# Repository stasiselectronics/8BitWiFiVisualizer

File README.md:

# 8 Bit WiFi Visualizer
Open Source Hardware project for a minimalist WiFi enabled 8 Bit visualizer. This design uses the popular ESP8266 wifi module to drive 8 LEDs with a shift register.
<h2><a href="https://stasiselectronics.github.io/8BitWiFiVisualizer/docs/">Check out the Docs!</a></h2>
<h2><a href="https://www.tindie.com/products/stasis/8-bit-wifi-visualizer/">Order on Tindie!</a></h2>

## Network Traffic Visualizer
Want to visualize how busy your WiFi channel is? The included Arduino sketch measures how many packets are flying around on the selected channel and displays the intensity on the LEDs.

With the help of some automated functions, the board selects the WiFi channel with the strongest network present at startup. It then automatically adjusts the display range to keep up with changing network conditions.

[Learn more about how this firmware works!](https://stasiselectronics.github.io/8BitWiFiVisualizer/docs/enclosure/automatic-firmware/)

This repository contains all the source files needed to reproduce this project. The PCB is designed with KiCAD and the firmware uses Arduino for the ESP8266.

This is still a work in progress, so be sure to check back for future updates!

## Companion Site
I've put together a Github pages site to host all the documentation that goes with this design. Learn more about how everything works and keep up to date with blog posts. 

<h4>This is still a work in progress, more to come!</h4>

[Check out the companion site for more documentation!](https://stasiselectronics.github.io/8BitWiFiVisualizer/)

## Quick Links
- [Board Schematics](https://github.com/stasiselectronics/8BitWiFiVisualizer/blob/master/Hardware%20Files/PDFs/8Bit_WiFi_Visualizer_Schematic.pdf)
- [Arduino Sketch](https://github.com/stasiselectronics/8BitWiFiVisualizer/blob/master/Firmware%20Files/PacketVisualizer_auto/PacketVisualizer_auto.ino)

## Current Status

This project is nearing completion, here are some of the latest updates
- Redesigned PCB for larger components to make hand soldering easier
- Assembled and tested latest PCB design
- Major firmware updates
    - Auto selecting AP channel on startup
    - Auto ranging intensity scale with linear decay
    - Change AP channel with user button

## Future Goals

Here's what needs to get done for this project:
- Complete Documentation

Most of the project is now complete, so now all that is left is to finish up the documentation

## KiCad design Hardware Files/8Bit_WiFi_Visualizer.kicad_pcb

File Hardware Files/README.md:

# Hardware Files

Here you can find all the files for the PCB design. The board is designed in KiCAD

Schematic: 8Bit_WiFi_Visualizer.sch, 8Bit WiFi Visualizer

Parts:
C1, C2, C4, C5: 1uF; C_1206_3216Metric_Pad1.42x1.75mm_HandSolder; Manufacturer PN CL31B105KCHNNNE; LCSC Order Number C13832
C3: 10uF; C_1206_3216Metric_Pad1.42x1.75mm_HandSolder; Manufacturer PN CL31B106KAHNNNE; LCSC Order Number C14860
D1, D2, D3, D4, D5, D6, D7, D8: LED; LED_1206_3216Metric_Pad1.42x1.75mm_HandSolder; Manufacturer PN LTST-C150TBKT; LCSC Order Number C125088
J1: USB_B_Micro; U-F-M5DD-Y-L; Manufacturer PN U-F-M5DD-Y-L; LCSC Order Number C91146
J2: Conn_01x04; PinHeader_1x04_P2.54mm_Vertical
J3, J4: Conn_01x01; MountingHole_3.2mm_M3_DIN965_Pad
R1, R2, R3, R4, R5: 10k; R_1206_3216Metric_Pad1.42x1.75mm_HandSolder; Manufacturer PN RC1206JR-0710KL; LCSC Order Number C136460
SW1: SW_Push_Dual; PTS645SK50SMTR92LFS; Manufacturer PN 1TS005F-2500-5001; LCSC Order Number C255812
SW2, SW3: SW_SPST; PTS636_SM25F_SMTR_LFS; Manufacturer PN 1TS002B-2700-5000-CT; LCSC Order Number C318844
U1: 3.3V 1A; SOT-223-3_TabPin2; Manufacturer PN AZ1117CH-3.3TRG1; LCSC Order Number C92102
U2: 74HC595; SOIC-16_3.9x9.9mm_P1.27mm; Manufacturer PN 74HC595D,118; LCSC Order Number C5947
U3: ESP-WROOM-02D; Manufacturer PN ESP-WROOM-02D; LCSC Order Number C473007

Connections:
+3V3: C2.1, C3.1, C4.1, R1.1, R2.1, R5.1, U1.2 (VO), U2.16 (VCC), U3.1
+5V: C1.1, J1.1 (VBUS), J2.1, U1.3 (VI)
/BOOT: R1.2, SW3.1 (A), U3.8
/CLEAR: U2.10 (~SRCLR), U3.4
/CLOCK: U2.11 (SRCLK), U3.10
/DATA: U2.14 (SER), U3.17
/ESP_EN: C5.1, R2.2, SW2.1 (A), U3.2
/ESP_RX: J2.3, U3.11
/ESP_TX: J2.2, U3.12
/LATCH: U2.12 (RCLK), U3.14
/LED_1: D1.2 (A), U2.15 (QA)
/LED_2: D2.2 (A), U2.1 (QB)
/LED_3: D3.2 (A), U2.2 (QC)
/LED_4: D4.2 (A), U2.3 (QD)
/LED_5: D5.2 (A), U2.4 (QE)
/LED_6: D6.2 (A), U2.5 (QF)
/LED_7: D7.2 (A), U2.6 (QG)
/LED_8: D8.2 (A), U2.7 (QH)
/OUTPUT_ENABLE: R3.2, U2.13 (~OE), U3.5
/RST: U3.15
/SW_1: R5.2, SW1.1, SW1.3, U3.3
GND: C1.2, C2.2, C3.2, C4.2, C5.2, D1.1 (K), D2.1 (K), D3.1 (K), D4.1 (K), D5.1 (K), D6.1 (K), D7.1 (K), D8.1 (K), J1.5 (GND), J1.6 (Shield), J2.4, J3.1, J4.1, R3.1, R4.2, SW1.2, SW1.4, SW2.2 (B), SW3.2 (B), U1.1 (GND), U2.8 (GND), U3.9, U3.13, U3.18, U3.19
unnamed: R4.1, U3.6

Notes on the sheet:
External pull down on GPIO15 for boot options
It is recommended that users do not solder Pad 19 to the base board. If users do want to solder it, they need to ensure that the correct quantity of soldering paste is applied.
Programming
User Switch
3.3V Power Supply
LED Driver
ESP8266 MCU
LEDs
Programming Header

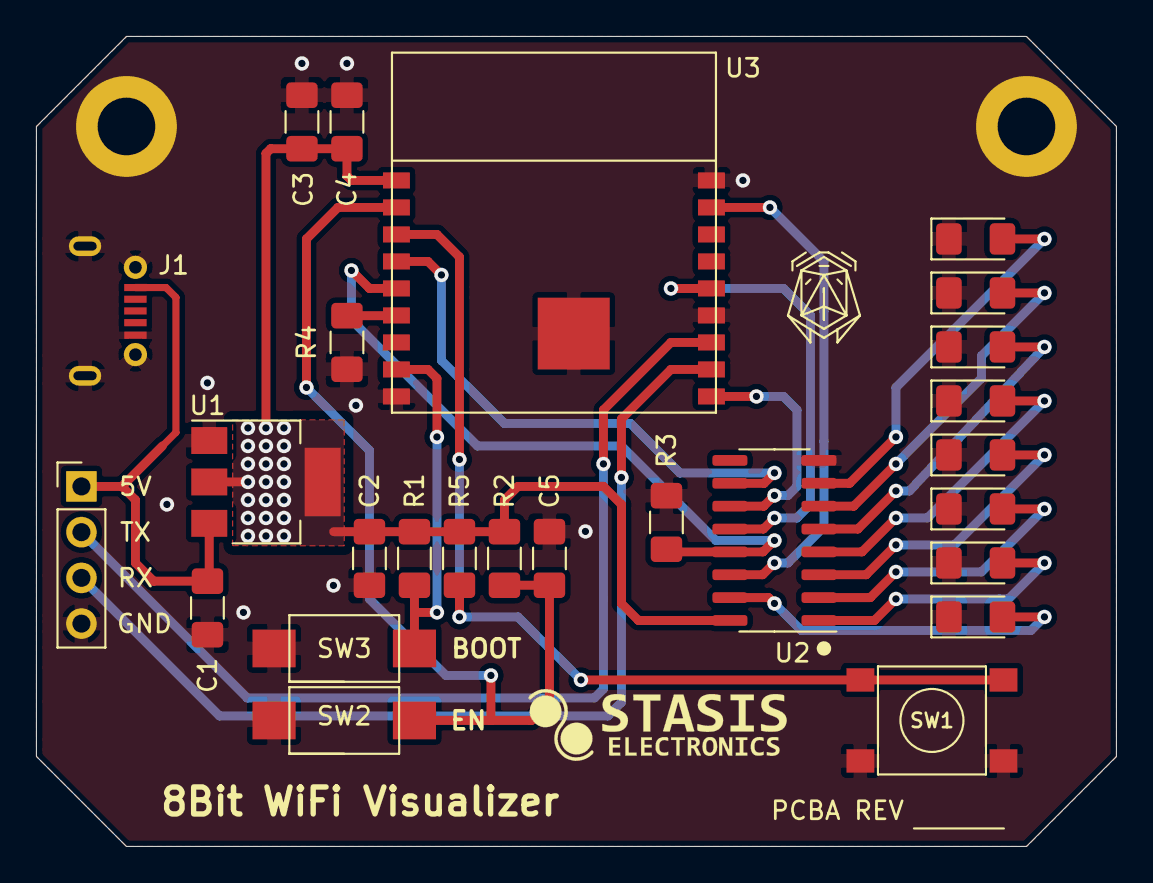
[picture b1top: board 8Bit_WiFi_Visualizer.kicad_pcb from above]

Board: 2 copper layers, 60.0 x 45.0 mm, 28 parts (0 on the bottom side), 22 nets.

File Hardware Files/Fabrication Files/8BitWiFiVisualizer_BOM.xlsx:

Component | References | Value | Description | LCSC Order Number | Manufacturer | Manufacturer PN | Quantity Per PCB | QTY per 100
1 | C1 C2 C4 C5 | 1uF | Unpolarized capacitor, small symbol | C13832 | Samsung Electro-Mechanics | CL31B105KCHNNNE | 4 | 400
2 | C3 | 10uF | Unpolarized capacitor, small symbol | C14860 | Samsung Electro-Mechanics | CL31B106KAHNNNE | 1 | 100
3 | D1 D2 D3 D4 D5 D6 D7 D8 | LED | Light emitting diode | C125088 | Lite-On | LTST-C150TBKT | 8 | 800
4 | J2 | Conn_01x04 | Generic connector, single row, 01x04 | C358686 | MINTRON | MTP125-1104S1 | 1 | 100
5 | J1 | USB_B_Micro | USB Micro Type B connector | C91146 | Korean Hroparts Elec | U-F-M5DD-Y-L | 1 | 100
6 | R1 R2 R3 R4 R5 | 10k | Resistor | C136460 | YAGEO | RC1206JR-0710KL | 5 | 500
7 | SW1 | SW_Push_Dual | Push button switch, generic, symbol, four pins | C255812 | Hongyuan Precision | 1TS005F-2500-5001 | 1 | 100
8 | SW2 SW3 | SW_SPST | Single Pole Single Throw (SPST) switch | C318844 | Hongyuan Precision | 1TS002B-2700-5000-CT | 2 | 200
9 | U1 | 3.3V 1A | 1A Low Dropout regulator, positive, 3.3V fixed output, SOT-223 | C92102 | Diodes Incorporated | AZ1117CH-3.3TRG1 | 1 | 100
10 | U2 | 74HC595 | 8-bit serial in/out Shift Register 3-State Outputs | C5947 | Nexperia | 74HC595D,118 | 1 | 100
11 | U3 | ESP-WROOM-02D |  | C473007 | Espressif Systems | ESP-WROOM-02D | 1 | 100

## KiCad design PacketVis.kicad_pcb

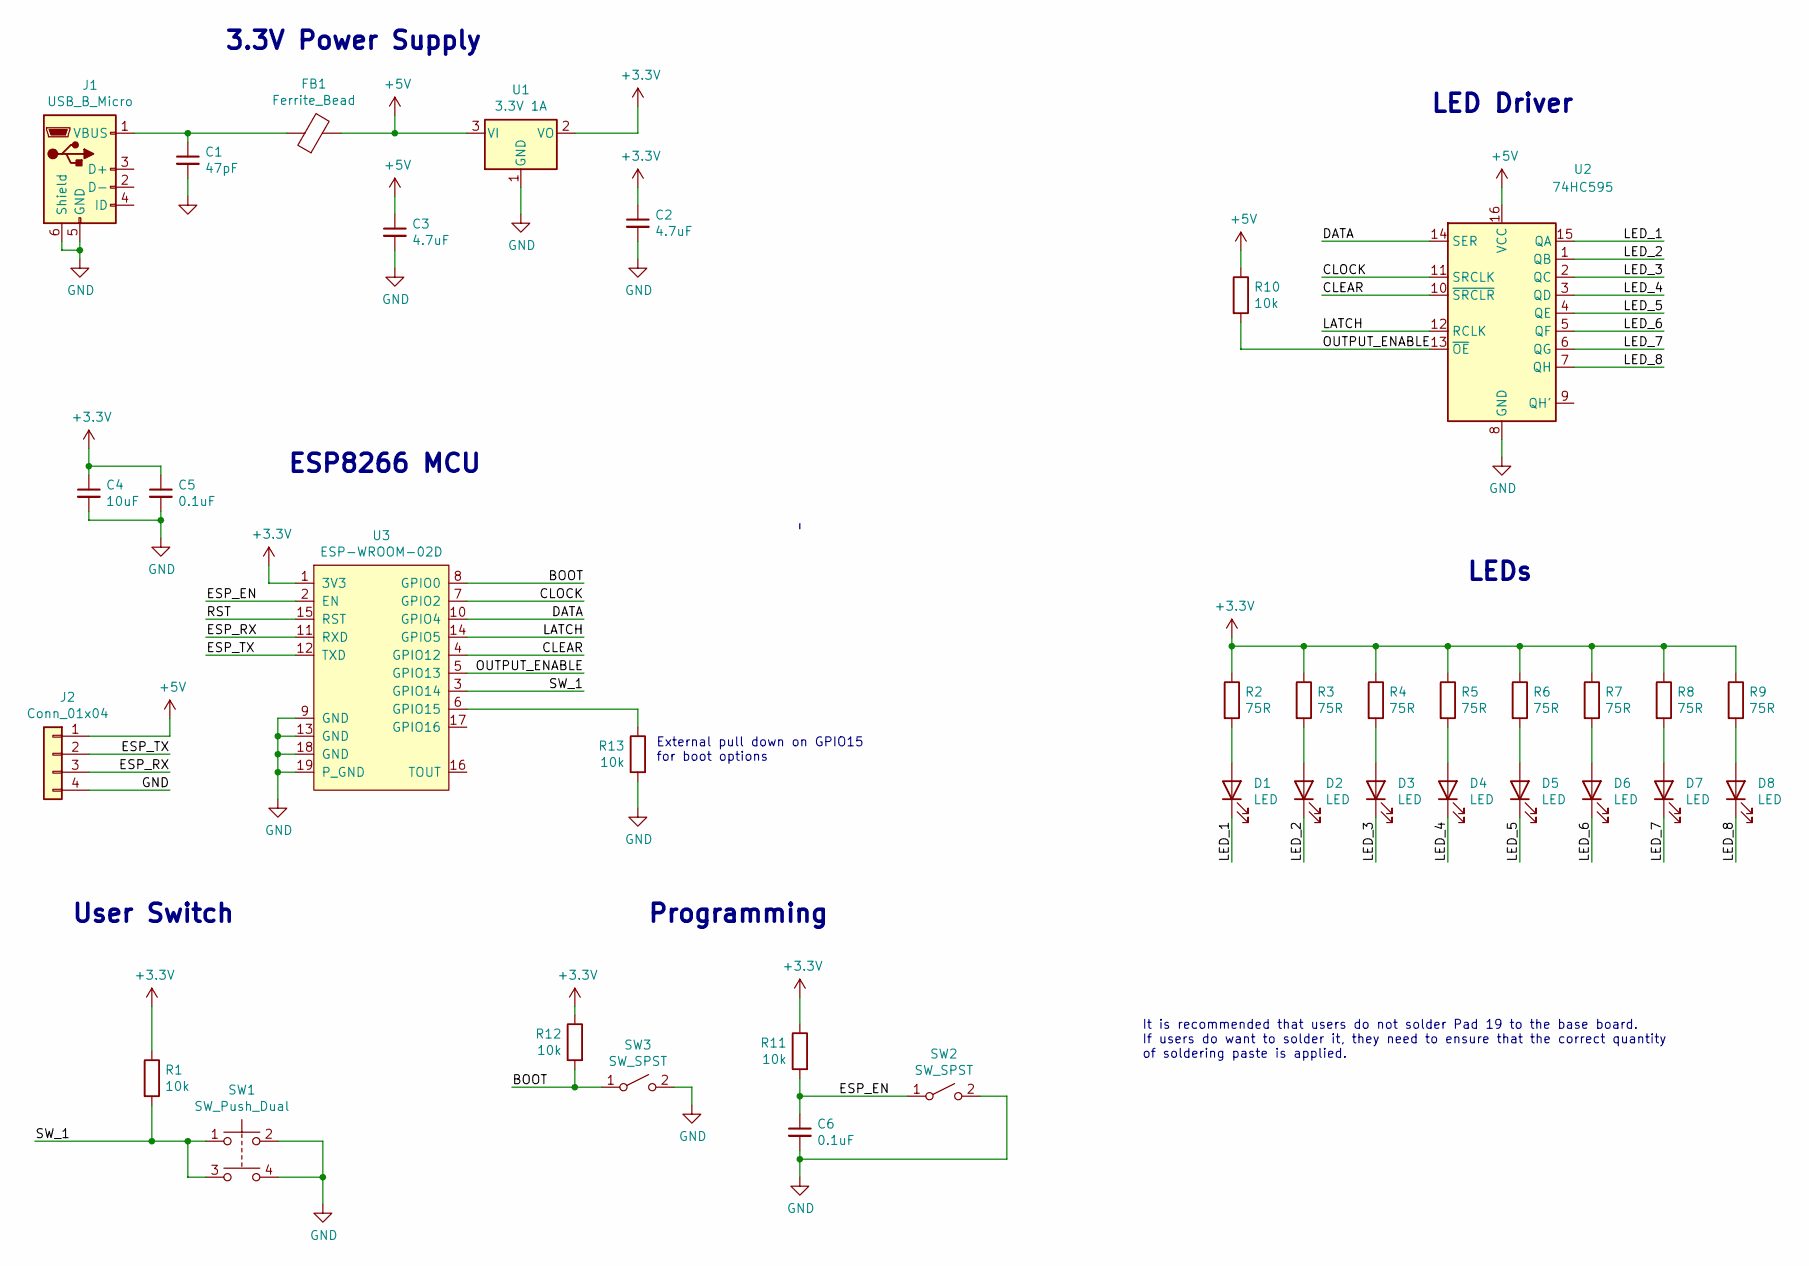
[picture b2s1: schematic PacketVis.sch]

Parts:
C1: 47pF; C_0805_2012Metric; Manufacturer PN CC0805JRNPO9BN470
C2, C3: 4.7uF; C_0805_2012Metric; Manufacturer PN CC0805ZRY5V6BB475
C4: 10uF; C_0805_2012Metric; Manufacturer PN CC0805ZKY5V5BB106
C5, C6: 0.1uF; C_0805_2012Metric; Manufacturer PN CC0805ZRY5V9BB104
D1, D2, D3, D4, D5, D6, D7, D8: LED; LED_0805_2012Metric_Castellated; Manufacturer PN LH R974-LP-1
FB1: Ferrite_Bead; L_0805_2012Metric; Manufacturer PN HI0805R800R-10
J1: USB_B_Micro; USB_Micro-B_Molex-105017-0001; Manufacturer PN 1050170001
J2: Conn_01x04; PinHeader_1x04_P2.54mm_Vertical
R1, R10, R11, R12, R13: 10k; R_0805_2012Metric; Manufacturer PN RC0805JR-0710KL
R2, R3, R4, R5, R6, R7, R8, R9: 75R; R_0805_2012Metric; Manufacturer PN RC0805FR-0775RL
SW1: SW_Push_Dual; PTS645SK50SMTR92 LFS; Manufacturer PN PTS645SK50SMTR92 LFS
SW2, SW3: SW_SPST; PTS636_SM25F_SMTR_LFS; Manufacturer PN PTS636 SM25F SMTR LFS
U1: 3.3V 1A; SOT-223-3_TabPin2; Manufacturer PN AP2114H-3.3TRG1
U2: 74HC595; SOIC-16; Manufacturer PN SN74HC595DR
U3: ESP-WROOM-02D; Manufacturer PN ESP-WROOM-02D

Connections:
+3V3: C2.1, C4.1, C5.1, R1.1, R2.1, R3.1, R4.1, R5.1, R6.1, R7.1, R8.1, R9.1, R11.1, R12.1, U1.2 (VO), U3.1 (3V3)
+5V: C3.1, FB1.2, J2.1, R10.1, U1.3 (VI), U2.16 (VCC)
/BOOT: R12.2, SW3.1 (A), U3.8 (GPIO0)
/CLEAR: U2.10 (~SRCLR), U3.4 (GPIO12)
/CLOCK: U2.11 (SRCLK), U3.7 (GPIO2)
/DATA: U2.14 (SER), U3.10 (GPIO4)
/ESP_EN: C6.1, R11.2, SW2.1 (A), U3.2 (EN)
/ESP_RX: J2.3, U3.11 (RXD)
/ESP_TX: J2.2, U3.12 (TXD)
/LATCH: U2.12 (RCLK), U3.14 (GPIO5)
/LED_1: D1.1 (K), U2.15 (QA)
/LED_2: D2.1 (K), U2.1 (QB)
/LED_3: D3.1 (K), U2.2 (QC)
/LED_4: D4.1 (K), U2.3 (QD)
/LED_5: D5.1 (K), U2.4 (QE)
/LED_6: D6.1 (K), U2.5 (QF)
/LED_7: D7.1 (K), U2.6 (QG)
/LED_8: D8.1 (K), U2.7 (QH)
/OUTPUT_ENABLE: R10.2, U2.13 (~OE), U3.5 (GPIO13)
/RST: U3.15 (RST)
/SW_1: R1.2, SW1.1, SW1.3, U3.3 (GPIO14)
GND: C1.2, C2.2, C3.2, C4.2, C5.2, C6.2, J1.5 (GND), J1.6 (Shield), J2.4, R13.2, SW1.2, SW1.4, SW2.2 (B), SW3.2 (B), U1.1 (GND), U2.8 (GND), U3.9 (GND), U3.13 (GND), U3.18 (GND), U3.19 (P_GND)
unnamed: C1.1, FB1.1, J1.1 (VBUS)
unnamed: D1.2 (A), R2.2
unnamed: D2.2 (A), R3.2
unnamed: D3.2 (A), R4.2
unnamed: D4.2 (A), R5.2
unnamed: D5.2 (A), R6.2
unnamed: D6.2 (A), R7.2
unnamed: D7.2 (A), R8.2
unnamed: D8.2 (A), R9.2
unnamed: R13.1, U3.6 (GPIO15)

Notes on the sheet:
External pull down on GPIO15 for boot options
It is recommended that users do not solder Pad 19 to the base board. If users do want to solder it, they need to ensure that the correct quantity of soldering paste is applied.
Programming
User Switch
3.3V Power Supply
LED Driver
ESP8266 MCU
LEDs

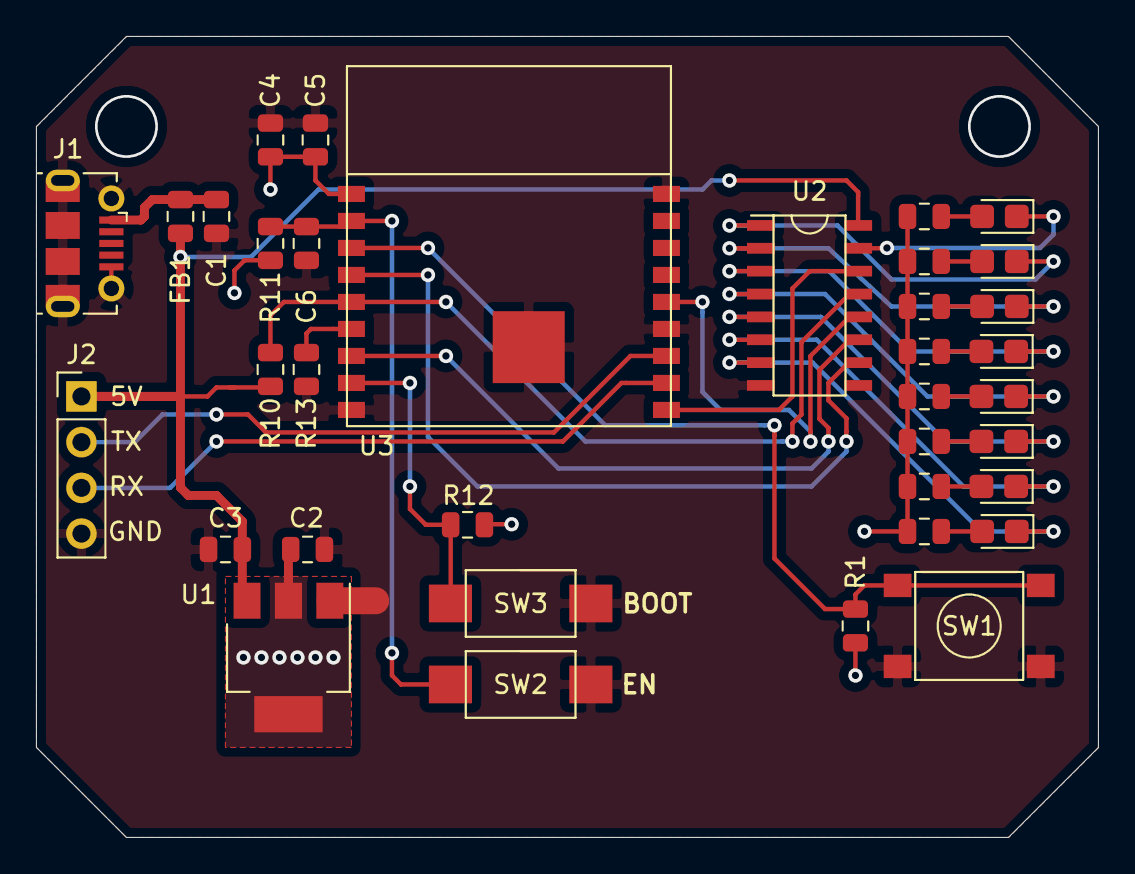
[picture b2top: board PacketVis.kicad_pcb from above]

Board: 2 copper layers, 59.0 x 44.5 mm, 36 parts (0 on the bottom side), 31 nets.

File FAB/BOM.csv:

C1,47pF,Capacitor_SMD:C_0805_2012Metric,~,CC0805JRNPO9BN470,1
">  C2, C3",4.7uF,Capacitor_SMD:C_0805_2012Metric,~,CC0805ZRY5V6BB475,2
    C4,10uF,Capacitor_SMD:C_0805_2012Metric,~,CC0805ZKY5V5BB106,1
">  C5, C6",0.1uF,Capacitor_SMD:C_0805_2012Metric,~,CC0805ZRY5V9BB104,2
>  D1-D8,LED,LED_SMD:LED_0805_2012Metric_Castellated,~,LH R974-LP-1,8
    FB1,Ferrite_Bead,Inductor_SMD:L_0805_2012Metric,~,HI0805R800R-10,1
    J1,USB_B_Micro,Connector_USB:USB_Micro-B_Molex-105017-0001,~,1050170001,1
    J2,Conn_01x03,Connector_PinHeader_2.54mm:PinHeader_1x03_P2.54mm_Vertical,~,,1
">  R1, R10-R13",10k,Resistor_SMD:R_0805_2012Metric,~,RC0805JR-0710KL,5
>  R2-R9,75R,Resistor_SMD:R_0805_2012Metric,~,RC0805FR-0775RL,8
    SW1,SW_Push_Dual,beginner_project_1_footprint_library:PTS645SK50SMTR92 LFS,~,PTS645SK50SMTR92 LFS,1
">  SW2, SW3",SW_SPST,beginner_project_1_footprint_library:PTS636_SM25F_SMTR_LFS,file:///C:/Users/A552123/Documents/KiCad%20Projects/beginner_project_1/beginner_project_1_footprint_library.pretty/datasheet.pdf,PTS636 SM25F SMTR LFS,2
    U1,3.3V 1A,Package_TO_SOT_SMD:SOT-223-3_TabPin2,https://www.diodes.com/assets/Datasheets/AP2114.pdf,AP2114H-3.3TRG1,1
    U2,74HC595,beginner_project_1_footprint_library:SOIC-16,http://www.ti.com/lit/ds/symlink/sn74hc595.pdf,SN74HC595DR,1
    U3,ESP-WROOM-02D,beginner_project_1_footprint_library:ESP-WROOM-02D,https://www.espressif.com/sites/default/files/documentation/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,ESP-WROOM-02D,1

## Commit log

2019-11-22 removing old project files
2019-11-25 Update Silkscreen
2020-03-02 Update SCH to A4 page size
2020-03-02 Update Routing
2020-03-10 Add 5V to Programming Header
2020-08-22 Changed U2 to 5v TTL Shift Register needs 5V instead of previous 3.3V Traces rerouted Added PCBA Step File
2020-08-22 Added Schematic PDF
2020-08-22 Updated Gerbers and Drills
2020-08-23 Fixed Missing REFS on PCB
2020-08-23 Fixed FAB Files
2020-08-24 Added ignore file
2020-09-11 Remove ignored files
2020-09-11 remove zip archive, use tags instead
2020-09-11 move 3D PCBA model
2020-09-11 Move Schematic PDF
2020-09-11 remove ignored file
2020-09-11 Move Fabrication Files
2020-09-11 update fabrication file output location
2020-09-11 upate BOM generation
2020-09-26 Change Shift Register back to 3.3V
2020-09-28 Move Files into Hardware Folder
2020-09-28 Upload Firmware
2020-09-28 Update comments
2020-09-28 Change LEDs to source current from shift register, unroute most tracks
2020-09-29 Rename Project Files
2020-09-29 Update Schematic Libraries
2020-09-29 Update Footprint Libraries
2020-09-29 Update Project Title
2020-09-29 Change filename
2020-09-29 Add 3D model to ESP02 footprint
2020-09-29 Update esp02 model on board
2020-09-29 add custom molex footprint with 3d model
2020-09-29 Update microusb to include 3D model
2020-09-29 Update SPST switch footprint to include 3D Model
2020-09-29 Update tactile switch footprint to include 3D model
2020-09-29 update PCBA 3D Model
2020-09-29 Add silkscreen layer
2020-09-29 Update Project Revision
2020-09-29 Cleanup Schematic
2020-09-29 add readme
2020-09-29 Change to 1206 components and reroute
2020-09-29 change components to 1206 footprints and remove some components
2020-09-30 Update Logo
2020-10-01 Reposition Reference Designators
2020-10-01 Re-Annotate Schematic
2020-10-01 Re-Annotate PCB
2020-10-01 add render image
2020-10-01 Add missing logo
2020-10-01 Rename and Update Schematic
2020-10-01 Update Gerbers
2020-10-01 Lock Logo to prevent deletion on update from schematic
2020-10-02 Scrub BOM details
2020-10-02 Add descriptions
2020-10-02 update part numbers
2020-10-02 fix USB MPN
2020-10-12 Add Stand Files
2020-10-15 Update pin mapping for A04
2020-10-15 add cut to nubs (are they really called nubs?)
2020-10-16 Add Adaptive Brightness
2020-10-17 Add button functions and autoscan RSSI
2020-10-17 Add basic firmware version
2020-10-17 Fix up basic firmware
2020-10-18 Add auto firmware
2020-10-18 update header comments
2020-10-18 Add auto scan for channel
2020-10-18 add auto brightness
2020-10-18 Add auto ranging
2020-10-18 Add low pass filter
2020-10-18 change filtering type
2020-10-18 add button functionality
2020-10-18 remove old version of firmware
2020-10-18 update startup functionality
2020-10-19 Clean Branch
2020-10-19 Copy Template
2020-10-19 Update homepage
2020-10-19 Remove template posts
2020-10-19 Change capacitors to 1uF
2020-10-19 Change USB connector and update revision
2020-10-19 Update part numbers and silkscreen
2020-10-19 Update Gerbers for A05
2020-10-19 add gerbers
2020-10-19 Updates for A05
2020-10-20 Move Logo and update GERBERS
2020-10-22 update index
2020-10-22 update quickstart
2020-10-22 update schematics page
2020-10-22 rearrange Schematic
2020-10-22 add image
2020-10-22 add schematic images
2020-10-22 update footer
2020-10-24 Add firmware pages
2020-10-24 update splash image
2020-10-24 update inde
2020-10-24 add pcba images
2020-10-24 add blog post
2020-10-24 update blog post
2020-10-25 update image
2020-10-25 rename files
2020-10-26 remove template files
2020-10-26 update docs page
2020-10-26 update docs
2020-10-26 update links and add new files
2020-10-26 fix links
2020-10-26 Update links and navigation bar
2020-10-26 update navigation bar
2020-10-26 fix links in navigation bar
2020-10-26 update about
2020-10-27 update assembly docs
2020-10-27 update components docs
2020-10-27 update layout docs
2020-10-28 Update LICENSE
    Changing to CERN Open Hardware License version 2
2020-10-28 add new stand design
2020-10-28 remove old stand files
2020-10-28 update schematic docs
2020-10-28 update schematics docs
2020-10-29 comment out debug
2020-10-29 update max rate logic
2020-10-29 comment out some debug
2020-10-30 add quantity to BOM
2020-10-30 add icon
2020-10-30 add favicon
2020-10-30 add custom head
2020-10-30 fix icon on subpages
2020-11-01 fix redirect link
2020-11-02 update firmware docs
2020-11-05 update assembly doc
2020-11-11 add new page layout file
2020-11-11 Update Title Block
2020-11-14 add gifs
2020-11-14 update firmware setup
2020-11-14 update firmware setup docs
2020-11-14 add images
2020-11-14 remove unnecessary files
2020-11-14 fix typo
2020-11-14 update links
2020-11-14 update landing page
2020-11-15 Add new template sketch
2020-11-15 update template firmware docs
2021-01-22 Minor Edits
2021-05-07 add BOM from microBBPS to use as a template
2021-05-07 update content to A05 board parts
2021-05-07 rename
2021-08-01 Add fix for AnalogWrite() range from 3.0.2 Arduino ESP8266 Core
2022-01-10 adjust naming
2022-01-10 add new BOM
2022-01-10 update content of BOM
2022-01-10 update name
2022-01-10 add export of Bill of Materials
